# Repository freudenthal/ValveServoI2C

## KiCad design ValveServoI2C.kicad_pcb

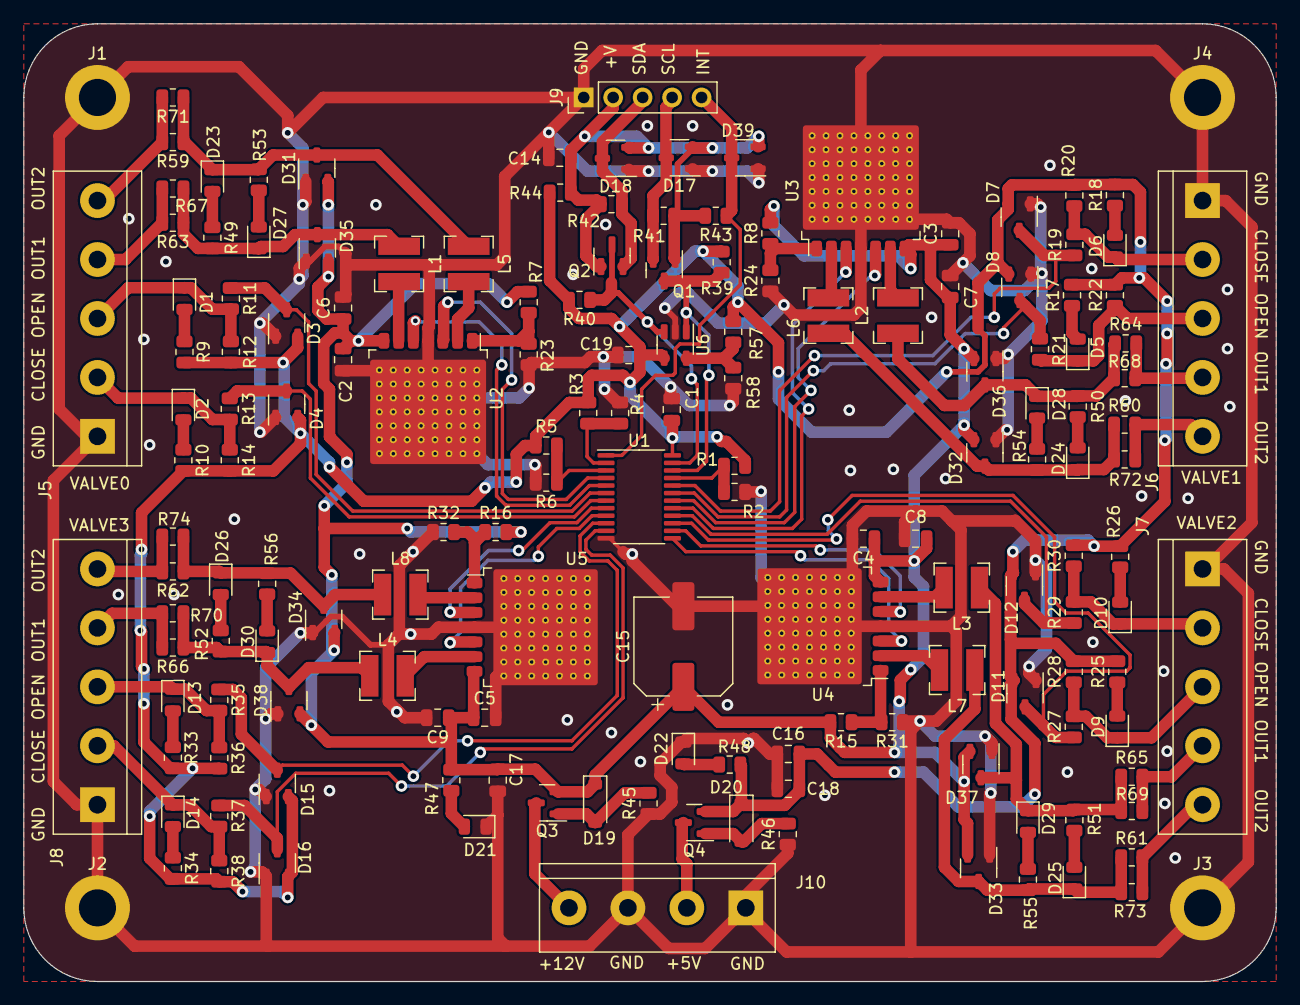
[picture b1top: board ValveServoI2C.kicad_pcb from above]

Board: 2 copper layers, 107.9 x 82.5 mm, 156 parts (0 on the bottom side), 87 nets.

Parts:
C1, C2, C3, C4, C5, C14, C17, C18, C19: 1uF; C_0805_2012Metric
C6, C7, C8, C9, C16: 10uF; C_0805_2012Metric
C15: 100uF; CP_Elec_8x11.9
D1, D2, D5, D6, D9, D10, D13, D14, D21, D22, D23, D24, D25, D26, D27, D28, D29, D30: LED; LED_0805_2012Metric
D3, D4, D7, D8, D11, D12, D15, D16, D17, D18, D31, D32, D33, D34, D35, D36, D37, D38, D39: 100V; SOT-23-3
D19, D20: 10V; D_SOD-123
J1, J2, J3, J4: M3; MountingHole_3.2mm_M3_DIN965_Pad
J5, J6, J7, J8: Valve; TerminalBlock_bornier-5_P5.08mm
J9: I2C; PinHeader_1x05_P2.54mm_Vertical
J10: VInput; TerminalBlock_bornier-4_P5.08mm
L1, L2, L3, L4, L5, L6, L7, L8: L; L_Bourns-SRN4018
Q1, Q2: Q_NMOS_GSD; SOT-23
Q3, Q4: Q_PMOS_GSD; SOT-23
R1, R2, R3, R4, R5, R6, R12, R14, R20, R22, R28, R30, R36, R38, R39, R40, R41, R42, R43, R57, R58: 10kΩ; R_0805_2012Metric
R7, R8, R15, R16: 1kΩ; R_0805_2012Metric
R9, R10, R17, R18, R25, R26, R33, R34, R47, R49, R50, R51, R52, R53, R54, R55, R56: 1.2kΩ; R_0805_2012Metric
R11, R13, R19, R21, R27, R29, R35, R37, R48: 500Ω; R_0805_2012Metric
R23, R24, R31, R32, R45, R46: 100kΩ; R_0805_2012Metric
R44: NS; R_0805_2012Metric
R59, R60, R61, R62, R63, R64, R65, R66, R67, R68, R69, R70, R71, R72, R73, R74: 10Ω; R_0805_2012Metric
U1: PCF8575; TSSOP-24_4.4x7.8mm_P0.65mm
U2, U3, U4, U5: BD6222HFP; Rohm_HRP7
U6: 24FC01T-I/OT; SOT-23-5

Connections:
+5V: C1.1, C16.1, C18.1, C19.1, D3.2 (K), D4.2 (K), D7.2 (K), D8.2 (K), D11.2 (K), D12.2 (K), D15.2 (K), D16.2 (K), D20.1 (K), Q4.2 (S), R1.1, R3.1, R5.1, R9.2, R10.2, R12.2, R14.2, R17.2, R18.2, R20.2, R22.2, R25.2, R26.2, R28.2, R30.2, R33.2, R34.2, R36.2, R38.2, R39.2, R40.2, R44.2, R48.2, R57.2, U1.24 (VDD), U6.4 (V_{CC})
+12V: C2.1, C3.1, C4.1, C5.1, C6.1, C7.1, C8.1, C9.1, C15.1, C17.1, D19.1 (K), D31.2 (K), D32.2 (K), D33.2 (K), D34.2 (K), D35.2 (K), D36.2 (K), D37.2 (K), D38.2 (K), Q3.2 (S), R7.2, R8.2, R15.2, R16.2, R47.2, U2.7 (V_{CC}), U3.7 (V_{CC}), U4.7 (V_{CC}), U5.7 (V_{CC})
/EEPROMI2C/SCL: Q1.3 (D), R39.1, U1.22 (SCL), U6.1 (SCL)
/EEPROMI2C/SDA: Q2.3 (D), R40.1, U1.23 (SDA), U6.3 (SDA)
/I2CConnector/INT: D39.3 (A), J9.5, R43.1, U1.1 (~INT)
/I2CConnector/VI2C: C14.1, D17.2 (K), D18.2 (K), D39.2 (K), J9.2, Q1.1 (G), Q2.1 (G), R41.2, R42.2, R43.2, R44.1
/PCF8575/A0: R1.2, R2.1, U1.21 (A0)
/PCF8575/A1: R3.2, R4.1, U1.2 (A1)
/PCF8575/A2: R5.2, R6.1, U1.3 (A2)
/PCF8575/ServoValveConnection1/DRV0: U1.17 (P14), U3.3 (F_{IN})
/PCF8575/ServoValveConnection1/DRV1: U1.18 (P15), U3.5 (R_{IN})
/PCF8575/ServoValveConnection1/DigitalPinIO2/Output: D5.1 (K), J6.3, R21.2, R22.1
/PCF8575/ServoValveConnection1/DigitalPinIO3/Output: D6.1 (K), J6.2, R19.2, R20.1
/PCF8575/ServoValveConnection1/END0: D8.3 (A), R21.1, U1.19 (P16)
/PCF8575/ServoValveConnection1/END1: D7.3 (A), R19.1, U1.20 (P17)
/PCF8575/ServoValveConnection2/DRV0: U1.13 (P10), U4.3 (F_{IN})
/PCF8575/ServoValveConnection2/DRV1: U1.14 (P11), U4.5 (R_{IN})
/PCF8575/ServoValveConnection2/DigitalPinIO2/Output: D9.1 (K), J7.3, R27.2, R28.1
/PCF8575/ServoValveConnection2/DigitalPinIO3/Output: D10.1 (K), J7.2, R29.2, R30.1
/PCF8575/ServoValveConnection2/END0: D11.3 (A), R27.1, U1.15 (P12)
/PCF8575/ServoValveConnection2/END1: D12.3 (A), R29.1, U1.16 (P13)
/PCF8575/ServoValveConnection3/DRV0: U1.8 (P04), U5.3 (F_{IN})
/PCF8575/ServoValveConnection3/DRV1: U1.9 (P05), U5.5 (R_{IN})
/PCF8575/ServoValveConnection3/DigitalPinIO2/Output: D13.1 (K), J8.3, R35.2, R36.1
/PCF8575/ServoValveConnection3/DigitalPinIO3/Output: D14.1 (K), J8.2, R37.2, R38.1
/PCF8575/ServoValveConnection3/END0: D15.3 (A), R35.1, U1.10 (P06)
/PCF8575/ServoValveConnection3/END1: D16.3 (A), R37.1, U1.11 (P07)
/PCF8575/ServoValveConnection/DRV0: U1.4 (P00), U2.3 (F_{IN})
/PCF8575/ServoValveConnection/DRV1: U1.5 (P01), U2.5 (R_{IN})
/PCF8575/ServoValveConnection/DigitalPinIO2/Output: D1.1 (K), J5.3, R11.2, R12.1
/PCF8575/ServoValveConnection/DigitalPinIO3/Output: D2.1 (K), J5.2, R13.2, R14.1
/PCF8575/ServoValveConnection/END0: D3.3 (A), R11.1, U1.6 (P02)
/PCF8575/ServoValveConnection/END1: D4.3 (A), R13.1, U1.7 (P03)
GND: C1.2, C2.2, C3.2, C4.2, C5.2, C6.2, C7.2, C8.2, C9.2, C14.2, C15.2, C16.2, C17.2, C18.2, C19.2, D3.1 (K), D4.1 (K), D7.1 (K), D8.1 (K), D11.1 (K), D12.1 (K), D15.1 (K), D16.1 (K), D17.1 (K), D18.1 (K), D21.1 (K), D22.1 (K), D31.1 (K), D32.1 (K), D33.1 (K), D34.1 (K), D35.1 (K), D36.1 (K), D37.1 (K), D38.1 (K), D39.1 (K), J1.1, J2.1, J3.1, J4.1, J5.1, J6.1, J7.1, J8.1, J9.1, J10.1, J10.3, R2.2, R4.2, R6.2, R23.1, R24.1, R31.1, R32.1, R45.1, R46.1, R58.1, U1.12 (VSS), U2.4 (GND), U3.4 (GND), U4.4 (GND), U5.4 (GND), U6.2 (GND)
unnamed: D1.2 (A), R9.1
unnamed: D2.2 (A), R10.1
unnamed: D5.2 (A), R17.1
unnamed: D6.2 (A), R18.1
unnamed: D9.2 (A), R25.1
unnamed: D10.2 (A), R26.1
unnamed: D13.2 (A), R33.1
unnamed: D14.2 (A), R34.1
unnamed: D17.3 (A), J9.4, Q1.2 (S), R41.1
unnamed: D18.3 (A), J9.3, Q2.2 (S), R42.1
unnamed: D19.2 (A), Q3.1 (G), R45.2
unnamed: D20.2 (A), Q4.1 (G), R46.2
unnamed: D21.2 (A), R47.1
unnamed: D22.2 (A), R48.1
unnamed: D23.2 (A), R49.1
unnamed: D23.1 (K), D31.3 (A), L5.2, R53.2, R59.1, R71.1
unnamed: D24.2 (A), R50.1
unnamed: D24.1 (K), D32.3 (A), L6.2, R54.2, R60.1, R72.1
unnamed: D25.2 (A), R51.1
unnamed: D25.1 (K), D33.3 (A), L7.2, R55.2, R61.1, R73.1
unnamed: D26.2 (A), R52.1
unnamed: D26.1 (K), D34.3 (A), L8.2, R56.2, R62.1, R74.1
unnamed: D27.2 (A), R53.1
unnamed: D27.1 (K), D35.3 (A), L1.2, R49.2, R63.1, R67.1
unnamed: D28.2 (A), R54.1
unnamed: D28.1 (K), D36.3 (A), L2.2, R50.2, R64.1, R68.1
unnamed: D29.2 (A), R55.1
unnamed: D29.1 (K), D37.3 (A), L3.2, R51.2, R65.1, R69.1
unnamed: D30.2 (A), R56.1
unnamed: D30.1 (K), D38.3 (A), L4.2, R52.2, R66.1, R70.1
unnamed: J5.4, R63.2, R67.2
unnamed: J5.5, R59.2, R71.2
unnamed: J6.4, R64.2, R68.2
unnamed: J6.5, R60.2, R72.2
unnamed: J7.4, R65.2, R69.2
unnamed: J7.5, R61.2, R73.2
unnamed: J8.4, R66.2, R70.2
unnamed: J8.5, R62.2, R74.2
unnamed: J10.2, Q4.3 (D)
unnamed: J10.4, Q3.3 (D)
unnamed: L5.1, U2.2 (OUT1)
unnamed: L1.1, U2.6 (OUT2)
unnamed: R7.1, R23.2, U2.1 (V_{REF})
unnamed: L6.1, U3.2 (OUT1)
unnamed: L2.1, U3.6 (OUT2)
unnamed: R8.1, R24.2, U3.1 (V_{REF})
unnamed: L7.1, U4.2 (OUT1)
unnamed: L3.1, U4.6 (OUT2)
unnamed: R15.1, R31.2, U4.1 (V_{REF})
unnamed: L8.1, U5.2 (OUT1)
unnamed: L4.1, U5.6 (OUT2)
unnamed: R16.1, R32.2, U5.1 (V_{REF})
unnamed: R57.1, R58.2, U6.5 (WP)

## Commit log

2023-11-12 Updated gate driver to BD6222 since the old one did not have enough current.
